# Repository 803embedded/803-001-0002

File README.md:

# 803-001-002-A - Digi cellular radio adapter for Toradex Viola

This KiCad 9 project is a native reconstruction of **803-001-001-B** from its released ODB++ manufacturing data. Connector and mounting-hole locations, board outline, signal routing, ground copper, and artwork are carried over from Rev B.

## Cellular modification

The original C3 10 uF / 1206 capacitor is replaced by:

- **C3: 220 uF, 16 V, polymer tantalum, 7343-31**
- KEMET `T521D227M016ATE025` (25 mΩ ESR)
- Digi-Key `399-T521D227M016ATE025CT-ND`

C3 is polarized; pad 1 / the marked end is VCC. Its center is shifted 0.94 mm left from the old C3 center to clear C2, and both pads have short 1.2 mm-wide connections into the unchanged VCC/GND copper.

TODO: update the below info

Digi's XBee Cellular 3G Global guide recommends at least 220 uF of bulk capacitance at VCC because cellular startup/wakeup inrush can approach 2 A. The existing 47 pF and 1 uF high-frequency bypass capacitors are retained. Reference:
<https://docs.digi.com/resources/documentation/digidocs/90001541/reference/r_cell_power_supply.htm>

## Validation notes

The schematic passes KiCad ERC with zero violations. Board DRC has zero errors. It retains warnings associated with the source reconstruction: legacy vector silkscreen contacts, custom footprints that intentionally differ from current KiCad library copies, and isolated same-net shapes carried over from ODB++. There are no unconnected items. The C3 area has no clearance, crossing, short-circuit, or unconnected-item violation. The WA-SMST spacer's intentional NPTH-in-copper construction is handled by two reference-scoped custom rules in `803-001-002-A.kicad_dru`.

## Project files

- `803-001-002-A.kicad_pro` - KiCad project
- `803-001-002-A.kicad_sch` - schematic
- `803-001-002-A.kicad_pcb` - two-layer PCB
- `803-001-002-A_BOM.csv` - assembly BOM

The XBee module itself is user-installed and is not part of the assembly BOM.

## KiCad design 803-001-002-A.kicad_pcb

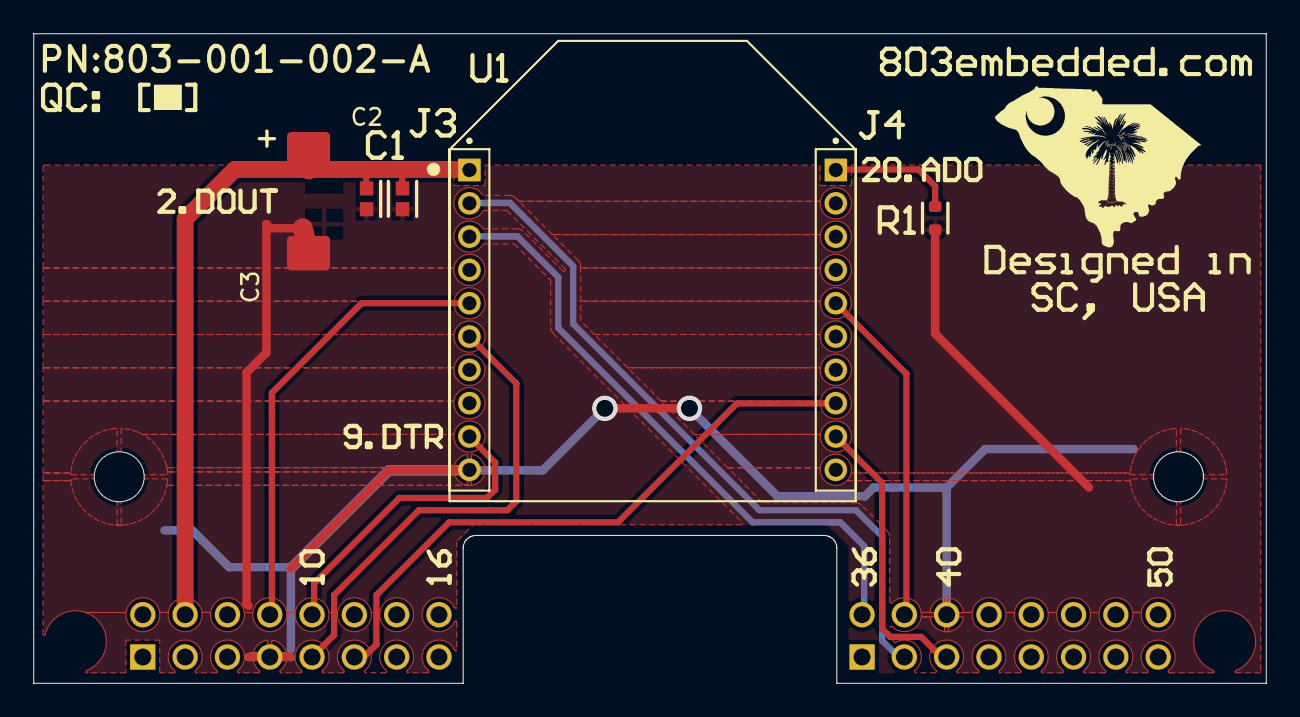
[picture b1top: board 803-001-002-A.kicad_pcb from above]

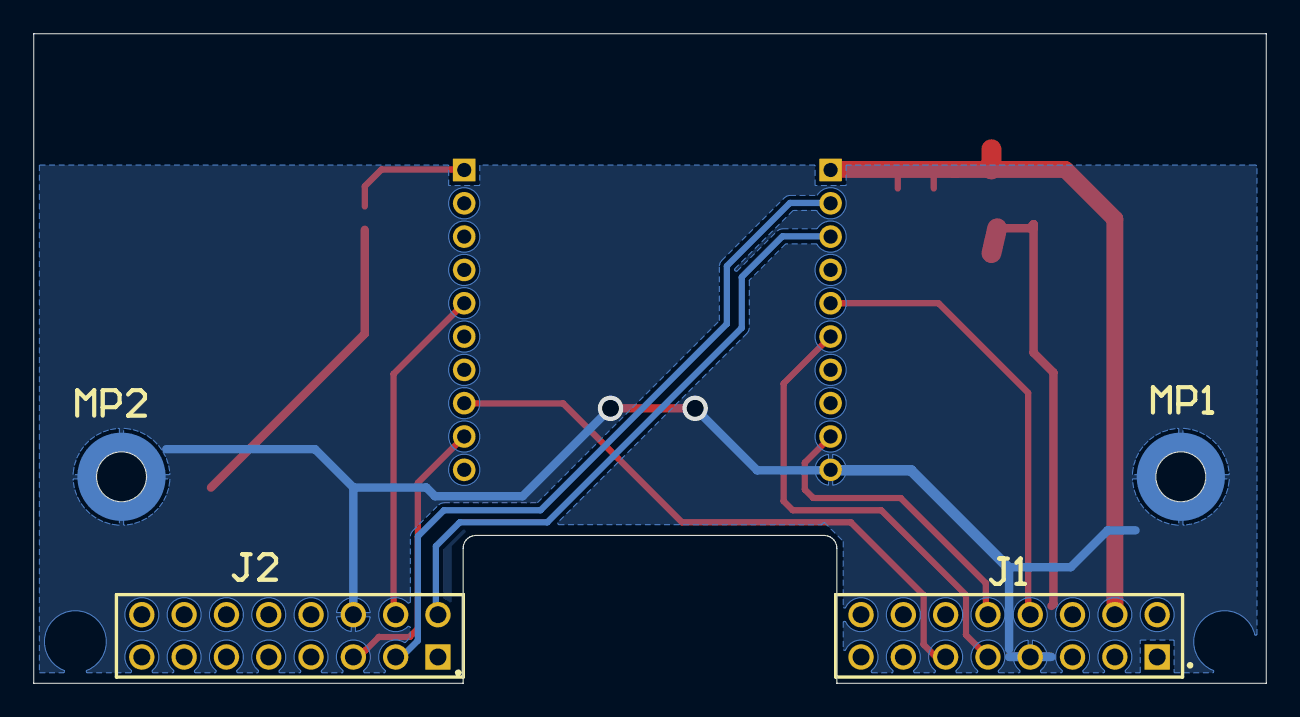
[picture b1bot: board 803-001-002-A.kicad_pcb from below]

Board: 2 copper layers, 74.0 x 39.0 mm, 10 parts (4 on the bottom side), 11 nets.

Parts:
C1: 47pF; C_0603_1608Metric
C2: 1uF; C_0603_1608Metric
C3: 220uF 16V; CP_EIA-7343-31_Kemet-D
J1, J2: SSQ-108-03-G-D; PinSocket_2x08_P2.54mm_Vertical
J3, J4: M22-7131042; PinSocket_1x10_P2.00mm_Vertical
MP1, MP2: 9774070943R; Mounting_Wuerth_WA-SMST-2.25mm_H7mm_9774070943
R1: 10k; R_0603_1608Metric

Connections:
AD0: J4.1, R1.2
CTS: J2.04, J4.5
DIN: J2.02, J3.3
DOUT: J2.03, J3.2
DTR: J1.10, J3.9
GND: C1.2, C2.2, C3.2, J1.07, J2.06, J3.10, MP1.1, MP2.1, R1.1
ON-SLEEP: J1.11, J4.8
RESET: J1.08, J3.5
RSSI: J1.09, J3.6
RTS: J2.05, J4.9
VCC: C1.1, C2.1, C3.1, J1.04, J3.1
